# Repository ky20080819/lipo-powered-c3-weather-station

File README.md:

# lipo-powered-c3-weather-station
upgraded version of c3-weather-station powered by esphome

## front view

### 2025.8.12 update: silk screen added

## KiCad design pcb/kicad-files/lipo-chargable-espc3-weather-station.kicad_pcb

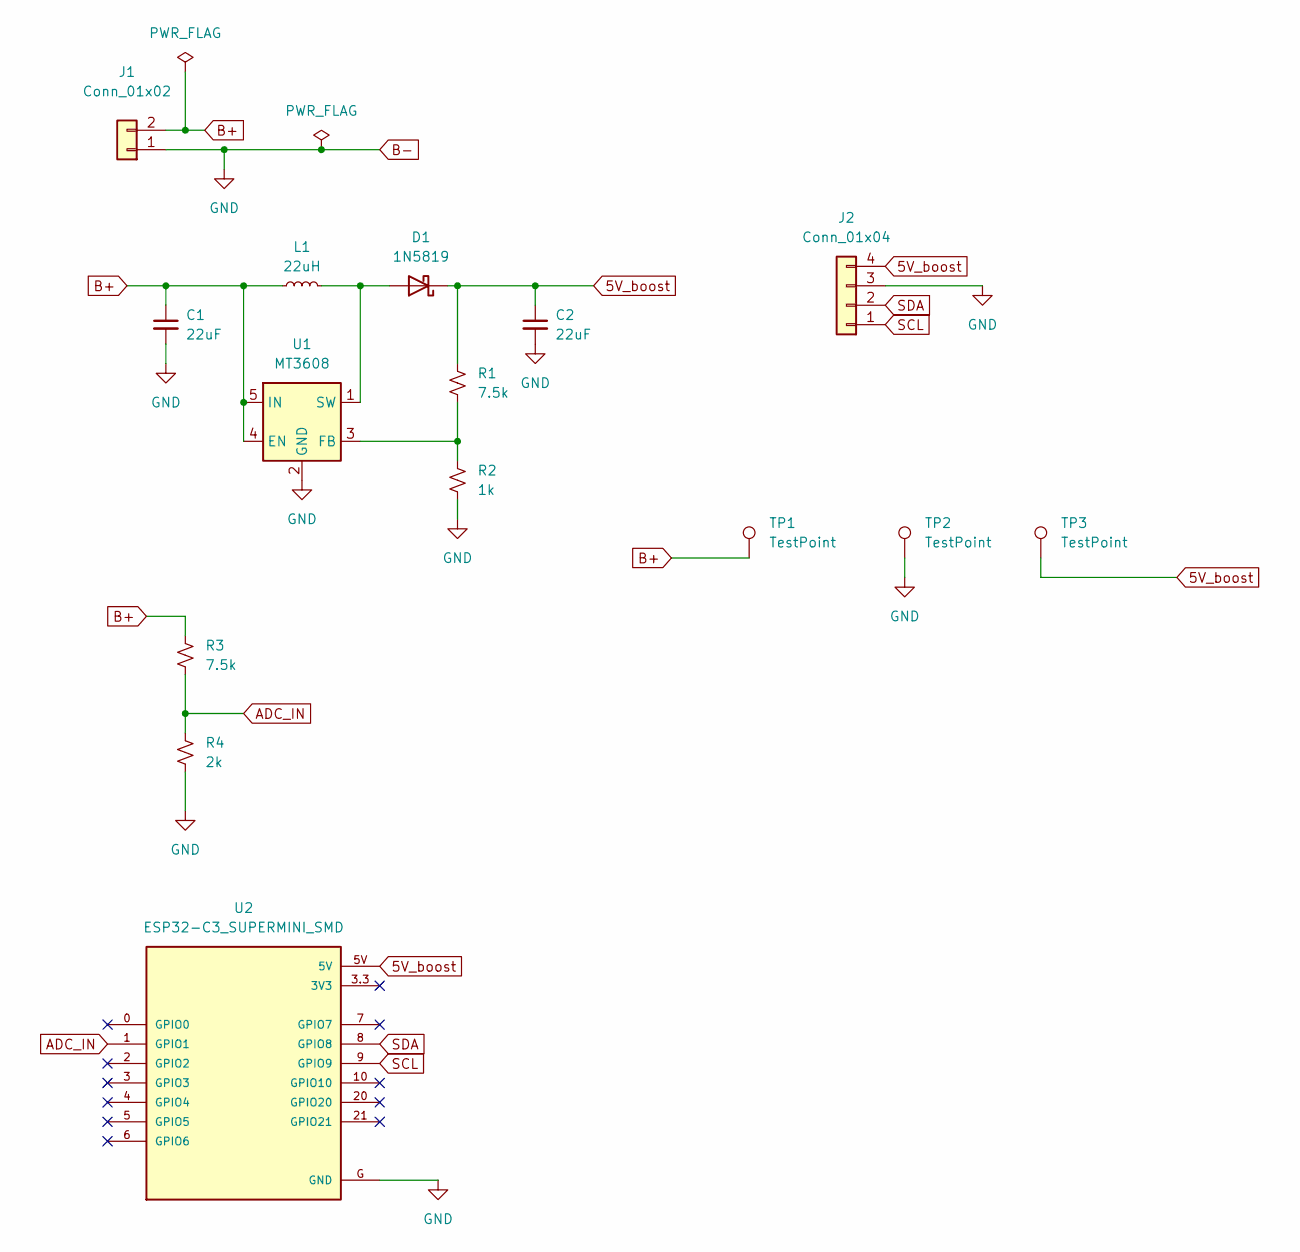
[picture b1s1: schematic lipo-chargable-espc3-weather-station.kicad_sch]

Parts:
C1, C2: 22uF; C_0805_2012Metric_Pad1.18x1.45mm_HandSolder
D1: 1N5819; D_SOD-123
J1: Conn_01x02; JST_PH_B2B-PH-K_1x02_P2.00mm_Vertical
J2: Conn_01x04; PinHeader_1x04_P2.54mm_Vertical
L1: 22uH; CD32_inductor
R1, R3: 7.5k; R_0805_2012Metric_Pad1.20x1.40mm_HandSolder
R2: 1k; R_0805_2012Metric_Pad1.20x1.40mm_HandSolder
R4: 2k; R_0805_2012Metric_Pad1.20x1.40mm_HandSolder
TP1, TP2, TP3: TestPoint; TestPoint_Pad_D2.0mm
U1: MT3608; SOT-23-6
U2: ESP32-C3_SUPERMINI_SMD; MODULE_ESP32-C3_SUPERMINI

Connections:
5V_boost: C2.1, D1.1 (K), J2.4, R1.1, TP3.1, U2.5V
ADC_IN: R3.2, R4.1, U2.1 (GPIO1)
B+: C1.1, J1.2, L1.1, R3.1, TP1.1, U1.4 (EN), U1.5 (IN)
B-: C1.2, C2.2, J1.1, J2.3, R2.2, R4.2, TP2.1, U1.2 (GND), U2.G (GND)
unnamed: D1.2 (A), L1.2, U1.1 (SW)
unnamed: R1.2, R2.1, U1.3 (FB)
SCL: J2.1, U2.9 (GPIO9)
SDA: J2.2, U2.8 (GPIO8)

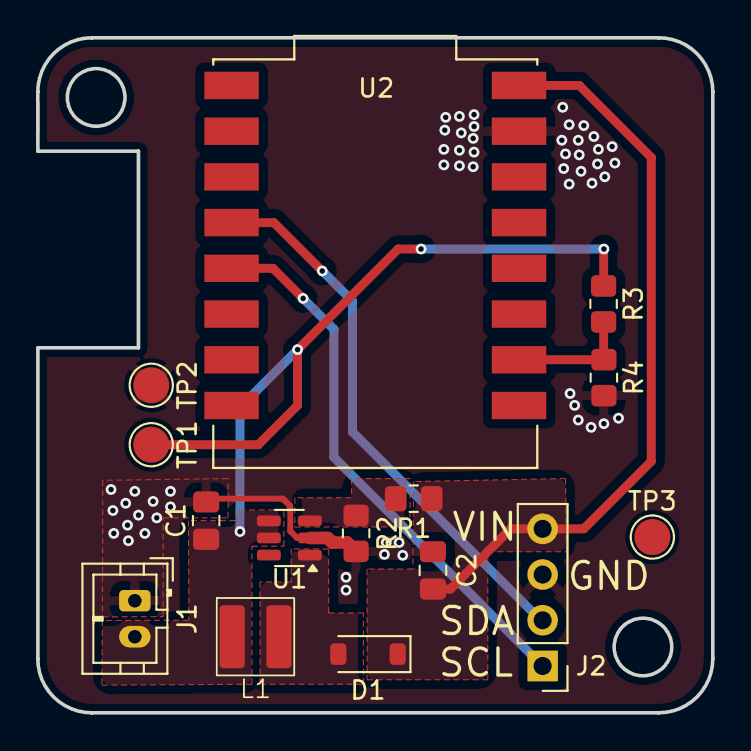
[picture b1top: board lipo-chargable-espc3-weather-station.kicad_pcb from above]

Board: 2 copper layers, 37.5 x 37.5 mm, 15 parts (0 on the bottom side), 8 nets.

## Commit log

2025-08-08 create image
2025-08-08 Rename 螢幕擷取畫面 2025-08-08 224317.png to image/螢幕擷取畫面 2025-08-08 224317.png
2025-08-08 Rename 螢幕擷取畫面 2025-08-08 224603.png to image/螢幕擷取畫面 2025-08-08 224603.png
2025-08-08 Rename 螢幕擷取畫面 2025-08-08 224624.png to image/螢幕擷取畫面 2025-08-08 224624.png
2025-08-08 Rename 螢幕擷取畫面 2025-08-08 224317.png to pcb-front.png
2025-08-08 Rename 螢幕擷取畫面 2025-08-08 224603.png to 3d-view-front.png
2025-08-08 Rename 螢幕擷取畫面 2025-08-08 224624.png to 3d-view-back.png
2025-08-12 Add files via upload
    silk screen added
2025-08-12 Rename 螢幕擷取畫面 2025-08-12 200552.png to 3d-view-back-silkscreen.png
